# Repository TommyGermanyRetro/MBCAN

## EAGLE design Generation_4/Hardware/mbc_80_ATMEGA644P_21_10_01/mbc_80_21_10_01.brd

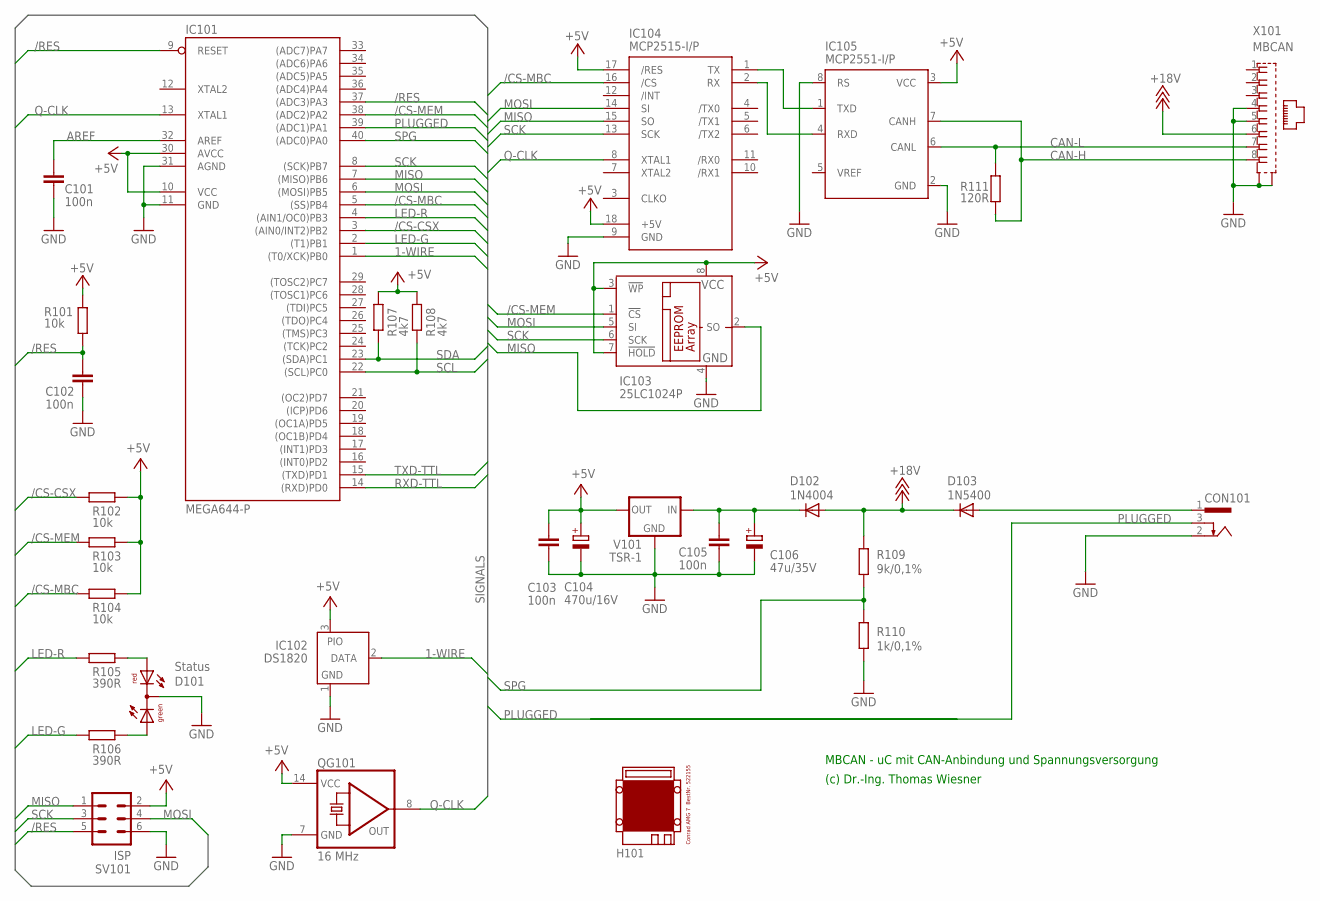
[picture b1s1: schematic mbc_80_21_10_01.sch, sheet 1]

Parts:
C101, C102, C103, C105: 100n; C025-025X050
C104: 470u/16V; E3,5-8
C106: 47u/35V; E2,5-7
CON101: POWER-JACK
D101: Status; DUOLED5MM
D102: 1N4004; DO41-10
D103: 1N5400; DO201-15
H101: MODULGEHÄUSE-AMG-7
IC101: MEGA644-P; DIL40
IC102: DS1820; TO92-
IC103: 25LC1024P; DIL8
IC104: MCP2515-I/P; DIL18
IC105: MCP2551-I/P; DIL08
QG101: 16 MHz; DIL14S
R101, R102, R103, R104: 10k; 0207/10
R105, R106: 390R; 0207/10
R107, R108: 4k7; 0207/10
R109: 9k/0,1%; 0207/10
R110: 1k/0,1%; 0207/10
R111: 120R; 0207/10
SV101: ISP; ML6
V101: TSR-1; TRACO-TSR-1
X101: MBCAN; 0446200002

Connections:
1-WIRE: IC101.1 ((T0/XCK)PB0), IC102.2 (DATA)
+5V: C103.1, C104.+, IC101.10 (VCC), IC101.30 (AVCC), IC102.3 (PIO), IC103.3 (!WP), IC103.7 (!HOLD), IC103.8 (VCC), IC104.17 (/RES), IC104.18 (+5V), IC105.3 (VCC), QG101.14 (VCC), R101.2, R102.2, R103.2, R104.2, R107.2, R108.2, SV101.2, V101.OUT; also elsewhere on the board
+18V: D102.A, D103.C, R109.1, X101.6
/CS-CSX: IC101.3 ((AIN0/INT2)PB2), R102.1; also elsewhere on the board
/CS-MBC: IC101.5 ((SS)PB4), IC104.16 (/CS), R104.1
/CS-MEM: IC101.38 ((ADC2)PA2), IC103.1 (!CS), R103.1
/RES: C102.1, IC101.9 (RESET), IC101.37 ((ADC3)PA3), R101.1, SV101.5
AREF: C101.1, IC101.32 (AREF)
CAN-H: IC105.7 (CANH), R111.1, X101.8
CAN-L: IC105.6 (CANL), R111.2, X101.7
GND: C101.2, C102.2, C103.2, C104.-, C105.2, C106.-, CON101.2, D101.K (C), IC101.11 (GND), IC101.31 (AGND), IC102.1 (GND), IC103.4 (GND), IC104.9 (GND), IC105.2 (GND), IC105.8 (RS), QG101.7 (GND), R110.2, SV101.6, V101.GND, X101.4, X101.5, X101.S@1 (S1), X101.S@2 (S2); also elsewhere on the board
LED-G: IC101.2 ((T1)PB1), R106.1
LED-R: IC101.4 ((AIN1/OC0)PB3), R105.1
MISO: IC101.7 ((MISO)PB6), IC103.2 (SO), IC104.15 (SO), SV101.1; also elsewhere on the board
MOSI: IC101.6 ((MOSI)PB5), IC103.5 (SI), IC104.14 (SI), SV101.4; also elsewhere on the board
unnamed: IC104.1 (TX), IC105.1 (TXD)
unnamed: IC104.2 (RX), IC105.4 (RXD)
unnamed: C105.1, C106.+, D102.C, V101.IN
unnamed: D101.AR, R105.2
unnamed: D101.AG, R106.2
PLUGGED: CON101.3, IC101.39 ((ADC1)PA1)
Q-CLK: IC101.13 (XTAL1), IC104.8 (XTAL1), QG101.8 (OUT); also elsewhere on the board
RXD-TTL: IC101.14 ((RXD)PD0); also elsewhere on the board
SCK: IC101.8 ((SCK)PB7), IC103.6 (SCK), IC104.13 (SCK), SV101.3; also elsewhere on the board
SCL: IC101.22 ((SCL)PC0), R108.1; also elsewhere on the board
SDA: IC101.23 ((SDA)PC1), R107.1; also elsewhere on the board
SPG: IC101.40 ((ADC0)PA0), R109.2, R110.1
TXD-TTL: IC101.15 ((TXD)PD1); also elsewhere on the board
V-NETZTEIL: CON101.1, D103.A

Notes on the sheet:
MBCAN - uC mit CAN-Anbindung und Spannungsversorgung
(c) Dr.-Ing. Thomas Wiesner

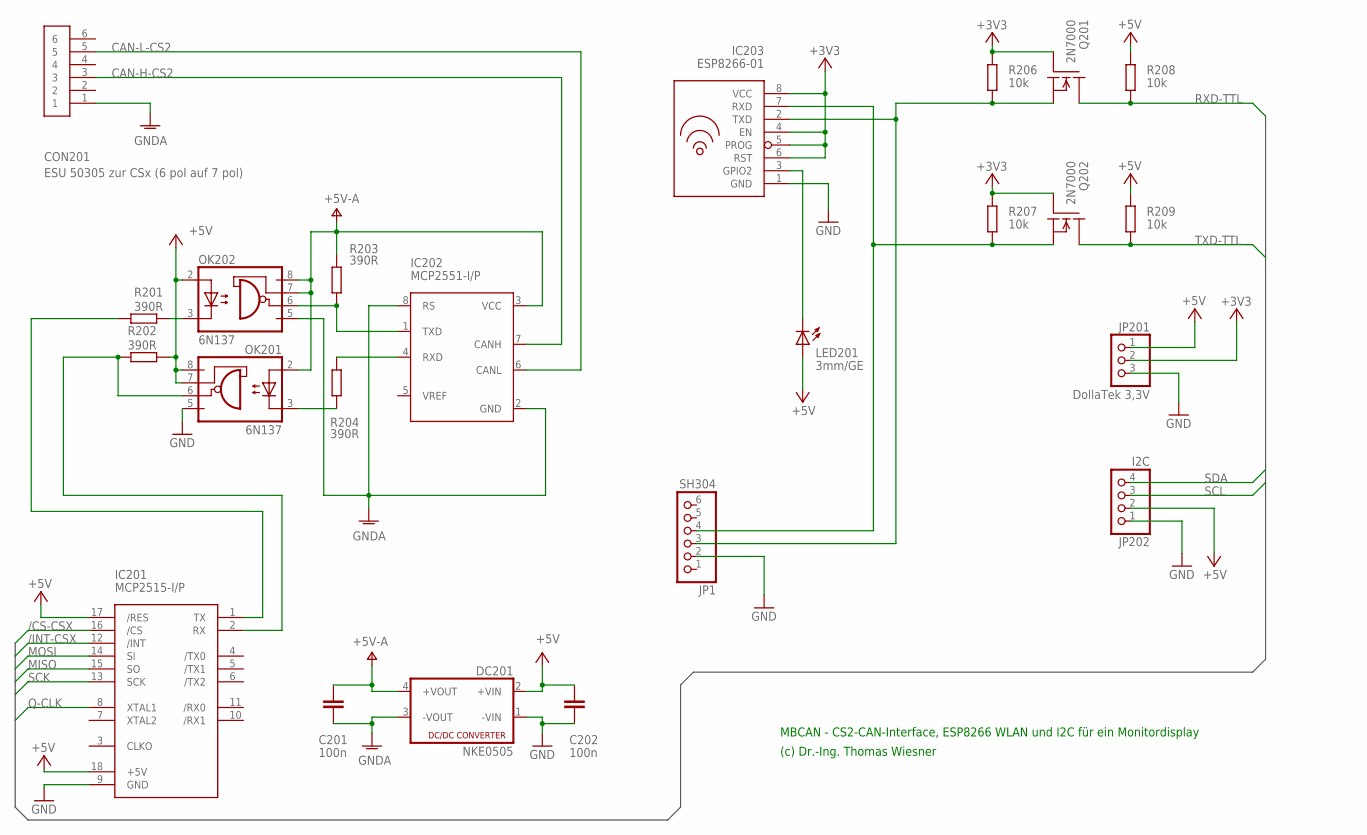
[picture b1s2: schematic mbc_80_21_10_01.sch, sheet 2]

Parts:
C201, C202: 100n; C025-025X050
CON201: ESU 50305 zur CSx (6 pol auf 7 pol); MINI-DIN-6-POL
DC201: NKE0505; NME
IC201: MCP2515-I/P; DIL18
IC202: MCP2551-I/P; DIL08
IC203: ESP8266-01
JP1: SH304; 1X06
JP201: DollaTek 3,3V; 1X03
JP202: I2C; 1X04
LED201: 3mm/GE; LED3MM
OK201, OK202: 6N137; DIL08
Q201, Q202: 2N7000; TO-92
R201, R202, R203, R204: 390R; 0207/10
R206, R207, R208, R209: 10k; 0207/10

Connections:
+3V3: IC203.4 (EN), IC203.5 (PROG), IC203.6 (RST), IC203.8 (VCC), JP201.2, Q201.2 (G), Q202.2 (G), R206.2, R207.2
+5V: C202.1, DC201.2 (+VIN), IC201.17 (/RES), IC201.18 (+5V), JP201.1, JP202.2, LED201.A, OK201.7 (VE), OK201.8 (VCC), OK202.2 (A), R202.2, R208.2, R209.2; also elsewhere on the board
+5V-A: C201.1, DC201.4 (+VOUT), IC202.3 (VCC), OK201.2 (A), OK202.7 (VE), OK202.8 (VCC), R203.2
/CS-CSX: IC201.16 (/CS); also elsewhere on the board
/INT-CSX: IC201.12 (/INT)
CAN-H-CS2: CON201.3, IC202.7 (CANH)
CAN-L-CS2: CON201.5, IC202.6 (CANL)
GND: C202.2, DC201.1 (-VIN), IC201.9 (GND), IC203.1 (GND), JP1.2, JP201.3, JP202.1, OK201.5 (GND); also elsewhere on the board
GNDA: C201.2, CON201.1, DC201.3 (-VOUT), IC202.2 (GND), IC202.8 (RS), OK202.5 (GND)
MISO: IC201.15 (SO); also elsewhere on the board
MOSI: IC201.14 (SI); also elsewhere on the board
unnamed: IC203.3 (GPIO2), LED201.K (C)
unnamed: IC203.2 (TXD), JP1.3, Q201.1 (S), R206.1
unnamed: IC203.7 (RXD), JP1.4, Q202.1 (S), R207.1
unnamed: IC201.1 (TX), R201.2
unnamed: IC202.1 (TXD), OK202.6 (VO), R203.1
unnamed: OK201.3 (C), R204.1
unnamed: IC202.4 (RXD), R204.2
unnamed: OK202.3 (C), R201.1
unnamed: IC201.2 (RX), OK201.6 (VO), R202.1
Q-CLK: IC201.8 (XTAL1); also elsewhere on the board
RXD-TTL: Q201.3 (D), R208.1; also elsewhere on the board
SCK: IC201.13 (SCK); also elsewhere on the board
SCL: JP202.3; also elsewhere on the board
SDA: JP202.4; also elsewhere on the board
TXD-TTL: Q202.3 (D), R209.1; also elsewhere on the board

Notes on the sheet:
(c) Dr.-Ing. Thomas Wiesner
MBCAN - CS2-CAN-Interface, ESP8266 WLAN und I2C für ein Monitordisplay

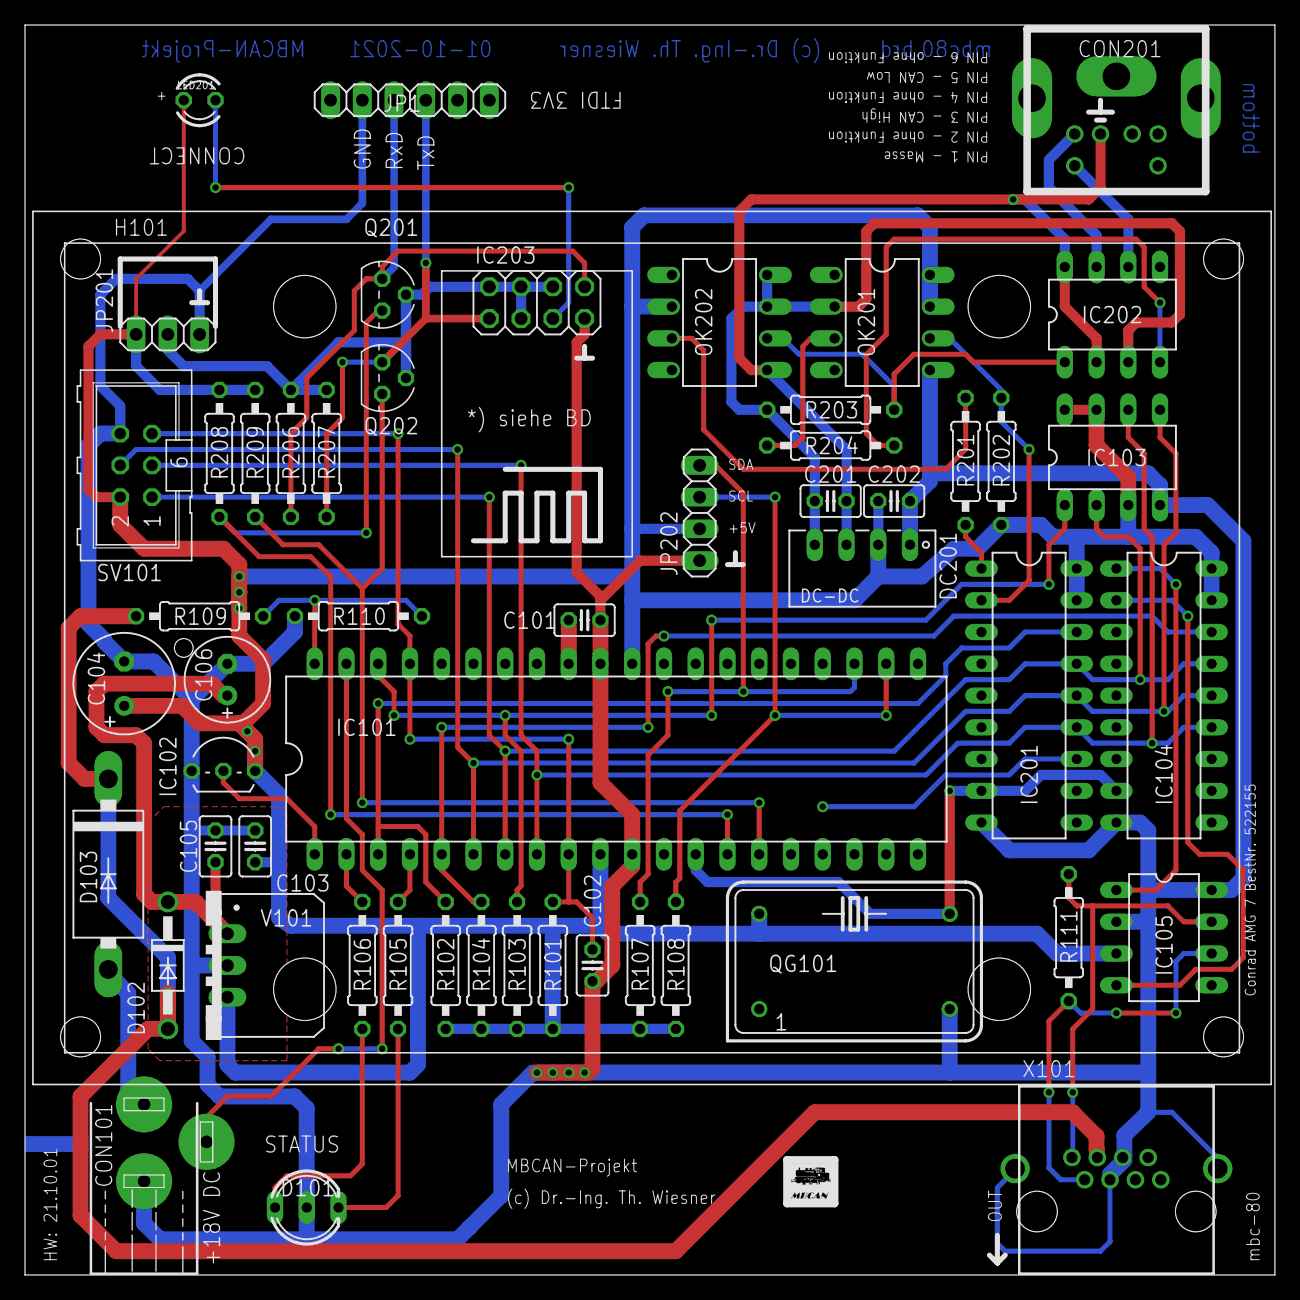
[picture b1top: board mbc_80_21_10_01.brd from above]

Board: 2 copper layers, 100.0 x 100.0 mm, 54 parts (0 on the bottom side), 43 nets.

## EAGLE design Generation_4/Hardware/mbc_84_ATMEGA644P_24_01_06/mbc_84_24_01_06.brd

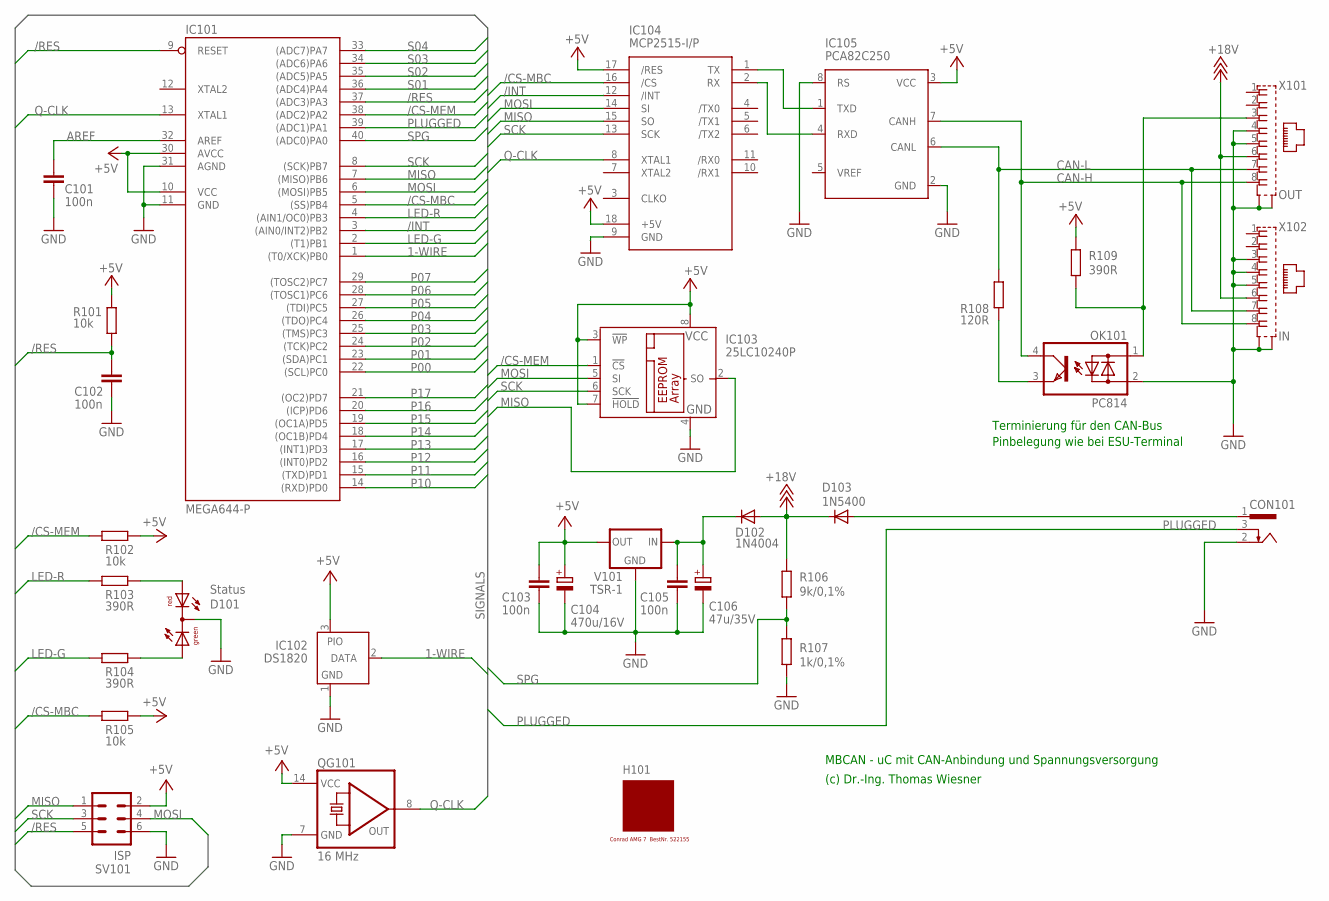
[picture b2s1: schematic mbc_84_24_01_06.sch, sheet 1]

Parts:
C101, C102, C103, C105: 100n; C025-025X050
C104: 470u/16V; E3,5-8
C106: 47u/35V; E2,5-7
CON101: POWER-JACK
D101: Status; DUOLED5MM
D102: 1N4004; DO41-10
D103: 1N5400; DO201-15
H101: MODULGEHÄUSE-AMG-7; MODULGEHÄUSE-1
IC101: MEGA644-P; DIL40
IC102: DS1820; TO92-
IC103: 25LC10240P; DIL8
IC104: MCP2515-I/P; DIL18
IC105: PCA82C250; DIL08
OK101: PC814; DIL04
QG101: 16 MHz; DIL14S
R101, R102, R105: 10k; 0207/10
R103, R104, R109: 390R; 0207/10
R106: 9k/0,1%; 0207/10
R107: 1k/0,1%; 0207/10
R108: 120R; 0207/10
SV101: ISP; ML6
V101: TSR-1; TRACO-TSR-1
X101: OUT; 0446200002
X102: IN; 0446200002

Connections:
1-WIRE: IC101.1 ((T0/XCK)PB0), IC102.2 (DATA)
+5V: C103.1, C104.+, IC101.10 (VCC), IC101.30 (AVCC), IC102.3 (PIO), IC103.3 (!WP), IC103.7 (!HOLD), IC103.8 (VCC), IC104.17 (/RES), IC104.18 (+5V), IC105.3 (VCC), QG101.14 (VCC), R101.2, R102.2, R105.2, R109.1, SV101.2, V101.OUT; also elsewhere on the board
+18V: D102.A, D103.C, R106.1, X101.6, X102.6; also elsewhere on the board
/CS-MBC: IC101.5 ((SS)PB4), IC104.16 (/CS), R105.1
/CS-MEM: IC101.38 ((ADC2)PA2), IC103.1 (!CS), R102.1
/INT: IC101.3 ((AIN0/INT2)PB2), IC104.12 (/INT)
/RES: C102.1, IC101.9 (RESET), IC101.37 ((ADC3)PA3), R101.1, SV101.5
AREF: C101.1, IC101.32 (AREF)
CAN-H: IC105.7 (CANH), OK101.4 (C), X101.8, X102.8
CAN-L: IC105.6 (CANL), R108.2, X101.7, X102.7
GND: C101.2, C102.2, C103.2, C104.-, C105.2, C106.-, CON101.2, D101.K (C), IC101.11 (GND), IC101.31 (AGND), IC102.1 (GND), IC103.4 (GND), IC104.9 (GND), IC105.2 (GND), IC105.8 (RS), OK101.2 (AC2), QG101.7 (GND), R107.2, SV101.6, V101.GND, X101.4, X101.5, X101.S@1 (S1), X101.S@2 (S2), X102.3, X102.4, X102.5, X102.S@1 (S1), X102.S@2 (S2); also elsewhere on the board
LED-G: IC101.2 ((T1)PB1), R104.1
LED-R: IC101.4 ((AIN1/OC0)PB3), R103.1
MISO: IC101.7 ((MISO)PB6), IC103.2 (SO), IC104.15 (SO), SV101.1
MOSI: IC101.6 ((MOSI)PB5), IC103.5 (SI), IC104.14 (SI), SV101.4
unnamed: IC104.1 (TX), IC105.1 (TXD)
unnamed: IC104.2 (RX), IC105.4 (RXD)
unnamed: OK101.3 (E), R108.1
unnamed: OK101.1 (AC1), R109.2, X101.3
unnamed: C105.1, C106.+, D102.C, V101.IN
unnamed: D101.AR, R103.2
unnamed: D101.AG, R104.2
P00: IC101.22 ((SCL)PC0); also elsewhere on the board
P01: IC101.23 ((SDA)PC1); also elsewhere on the board
P02: IC101.24 ((TCK)PC2); also elsewhere on the board
P03: IC101.25 ((TMS)PC3); also elsewhere on the board
P04: IC101.26 ((TDO)PC4); also elsewhere on the board
P05: IC101.27 ((TDI)PC5); also elsewhere on the board
P06: IC101.28 ((TOSC1)PC6); also elsewhere on the board
P07: IC101.29 ((TOSC2)PC7); also elsewhere on the board
P10: IC101.14 ((RXD)PD0); also elsewhere on the board
P11: IC101.15 ((TXD)PD1); also elsewhere on the board
P12: IC101.16 ((INT0)PD2); also elsewhere on the board
P13: IC101.17 ((INT1)PD3); also elsewhere on the board
P14: IC101.18 ((OC1B)PD4); also elsewhere on the board
P15: IC101.19 ((OC1A)PD5); also elsewhere on the board
P16: IC101.20 ((ICP)PD6); also elsewhere on the board
P17: IC101.21 ((OC2)PD7); also elsewhere on the board
PLUGGED: CON101.3, IC101.39 ((ADC1)PA1)
Q-CLK: IC101.13 (XTAL1), IC104.8 (XTAL1), QG101.8 (OUT)
S01: IC101.36 ((ADC4)PA4); also elsewhere on the board
S02: IC101.35 ((ADC5)PA5); also elsewhere on the board
S03: IC101.34 ((ADC6)PA6); also elsewhere on the board
S04: IC101.33 ((ADC7)PA7); also elsewhere on the board
SCK: IC101.8 ((SCK)PB7), IC103.6 (SCK), IC104.13 (SCK), SV101.3
SPG: IC101.40 ((ADC0)PA0), R106.2, R107.1
V-NETZTEIL1: CON101.1, D103.A

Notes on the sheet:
MBCAN - uC mit CAN-Anbindung und Spannungsversorgung
(c) Dr.-Ing. Thomas Wiesner
Terminierung für den CAN-Bus
Pinbelegung wie bei ESU-Terminal

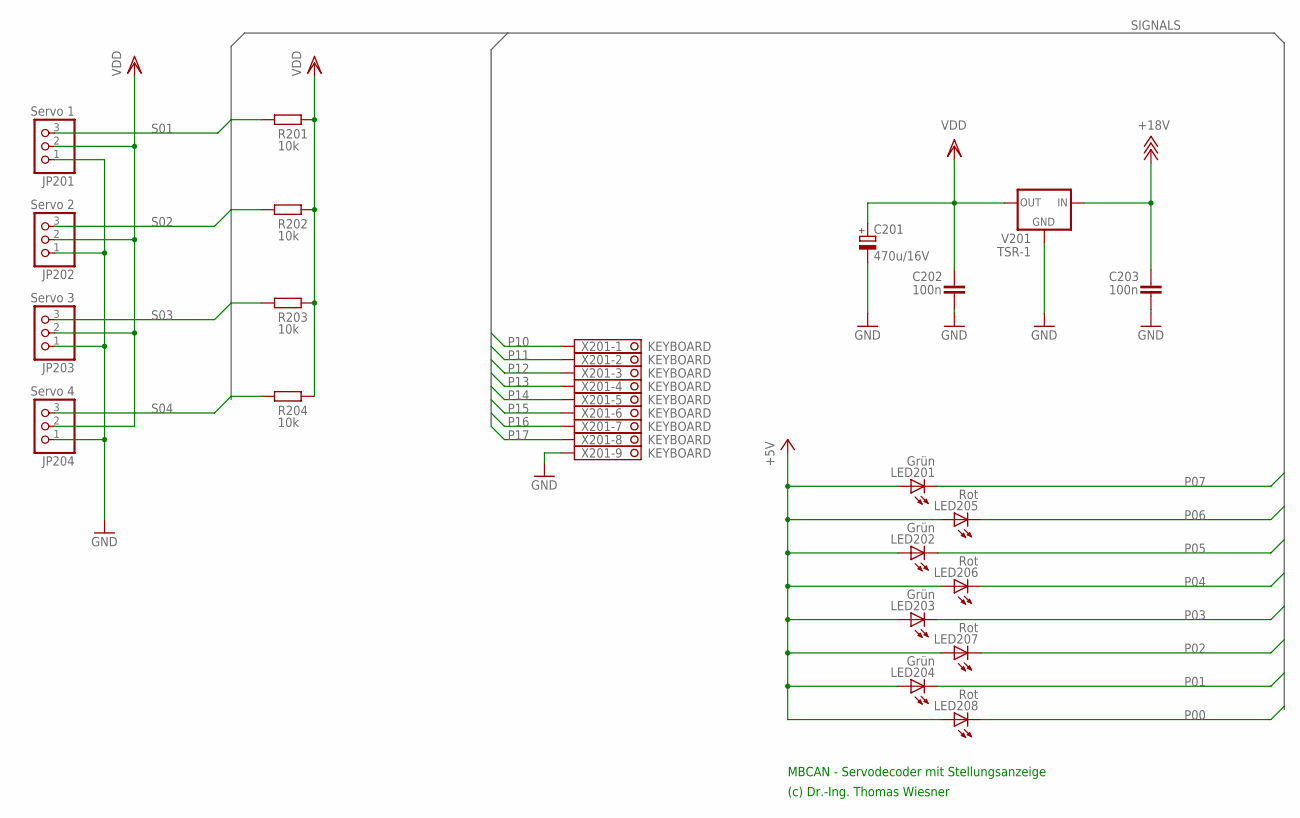
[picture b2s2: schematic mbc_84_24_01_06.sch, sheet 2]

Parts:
C201: 470u/16V; E3,5-8
C202, C203: 100n; C025-025X050
JP201: Servo 1; 1X03
JP202: Servo 2; 1X03
JP203: Servo 3; 1X03
JP204: Servo 4; 1X03
LED201, LED202, LED203, LED204: Grün; LED3MM
LED205, LED206, LED207, LED208: Rot; LED3MM
R201, R202, R203, R204: 10k; 0207/10
V201: TSR-1; TRACO-TSR-1
X201: KEYBOARD; 1751316

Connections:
+5V: LED201.A, LED202.A, LED203.A, LED204.A, LED205.A, LED206.A, LED207.A, LED208.A; also elsewhere on the board
+18V: C203.1, V201.IN; also elsewhere on the board
GND: C201.-, C202.2, C203.2, JP201.1, JP202.1, JP203.1, JP204.1, V201.GND, X201.9; also elsewhere on the board
P00: LED208.K (C); also elsewhere on the board
P01: LED204.K (C); also elsewhere on the board
P02: LED207.K (C); also elsewhere on the board
P03: LED203.K (C); also elsewhere on the board
P04: LED206.K (C); also elsewhere on the board
P05: LED202.K (C); also elsewhere on the board
P06: LED205.K (C); also elsewhere on the board
P07: LED201.K (C); also elsewhere on the board
P10: X201.1; also elsewhere on the board
P11: X201.2; also elsewhere on the board
P12: X201.3; also elsewhere on the board
P13: X201.4; also elsewhere on the board
P14: X201.5; also elsewhere on the board
P15: X201.6; also elsewhere on the board
P16: X201.7; also elsewhere on the board
P17: X201.8; also elsewhere on the board
S01: JP201.3, R201.1; also elsewhere on the board
S02: JP202.3, R202.1; also elsewhere on the board
S03: JP203.3, R203.1; also elsewhere on the board
S04: JP204.3, R204.1; also elsewhere on the board
VDD: C201.+, C202.1, JP201.2, JP202.2, JP203.2, JP204.2, R201.2, R202.2, R203.2, R204.2, V201.OUT

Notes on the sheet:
MBCAN - Servodecoder mit Stellungsanzeige
(c) Dr.-Ing. Thomas Wiesner

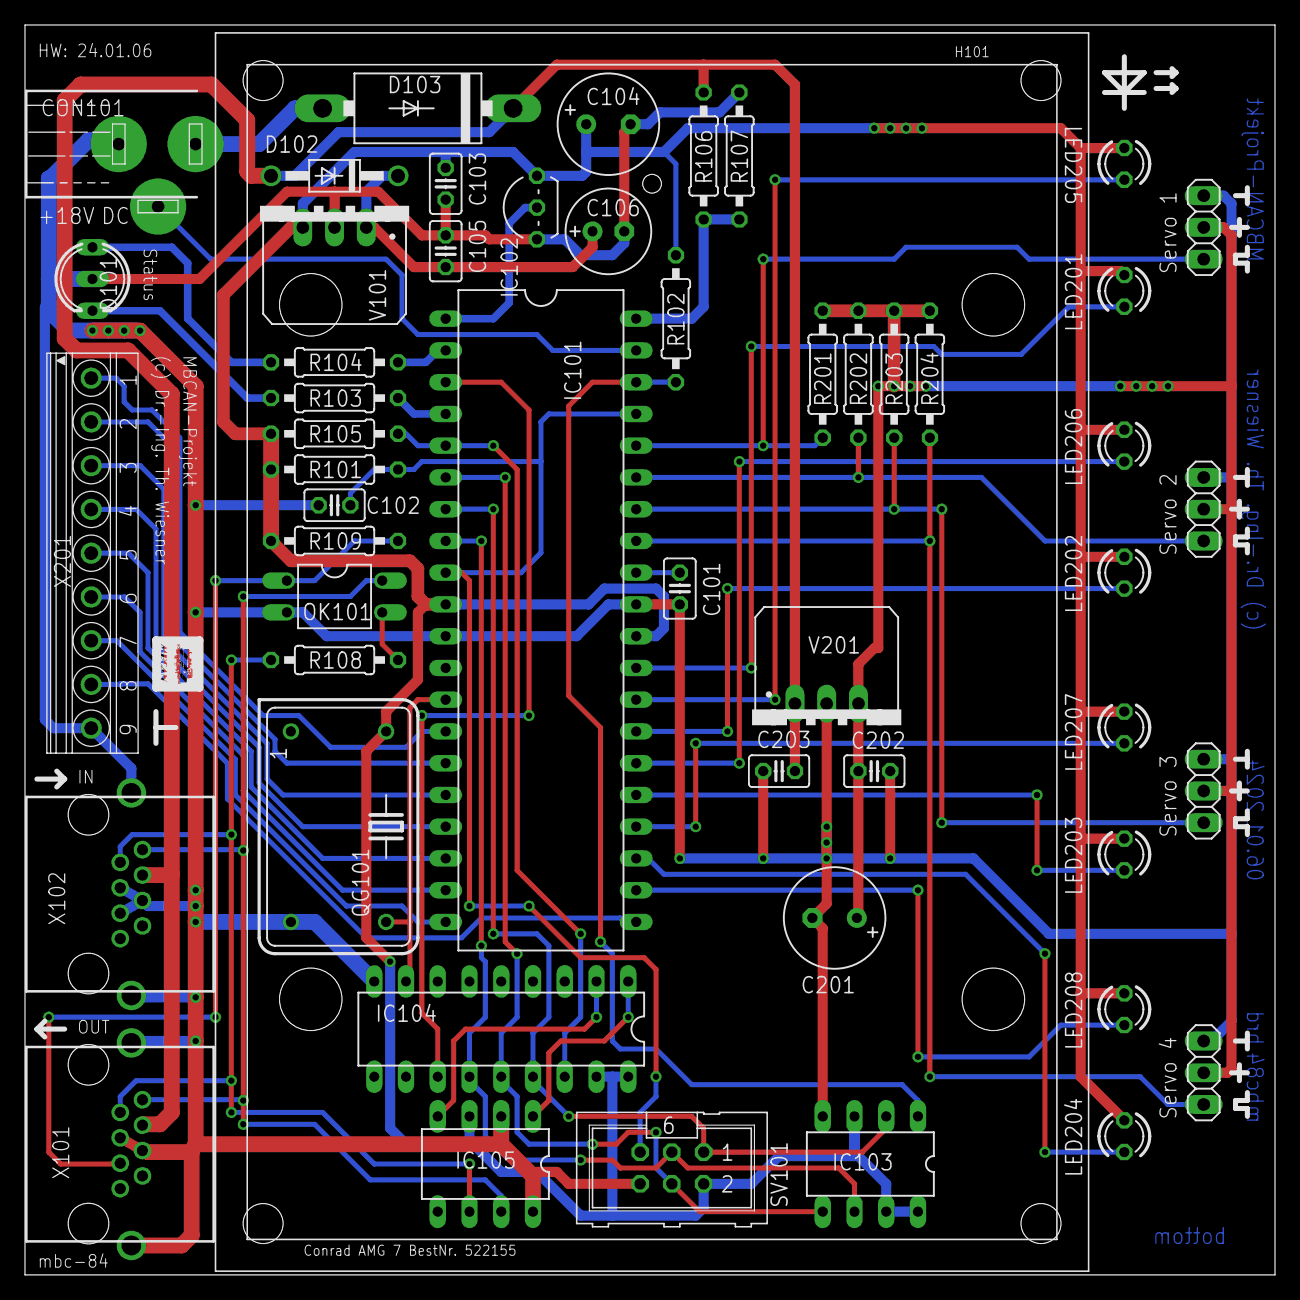
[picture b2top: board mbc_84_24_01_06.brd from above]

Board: 2 copper layers, 100.0 x 100.0 mm, 52 parts (0 on the bottom side), 48 nets.

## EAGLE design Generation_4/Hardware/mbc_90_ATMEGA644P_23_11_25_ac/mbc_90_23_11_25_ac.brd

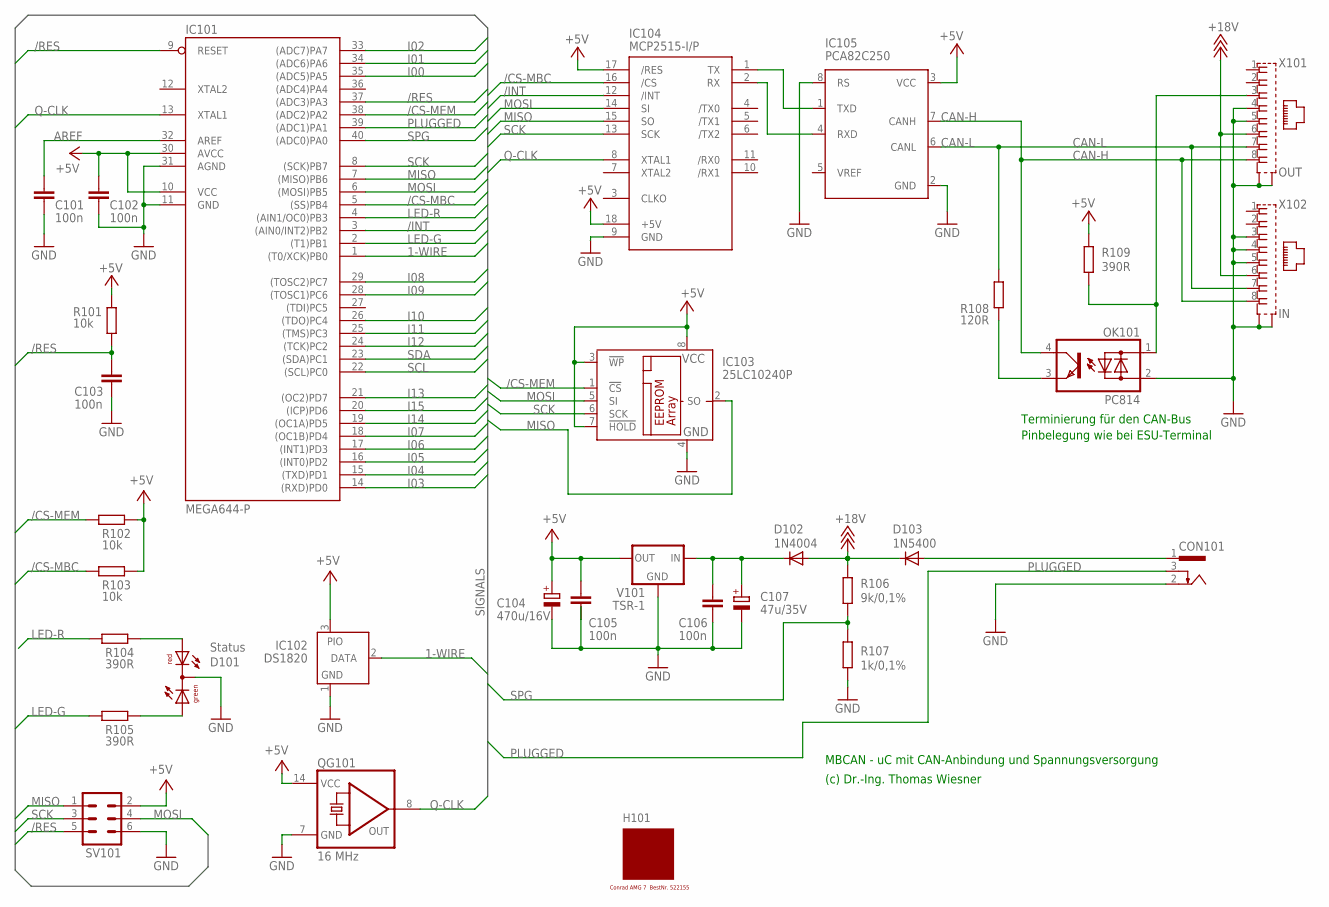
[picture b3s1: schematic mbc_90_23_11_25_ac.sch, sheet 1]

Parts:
C101, C102, C103, C105, C106: 100n; C025-025X050
C104: 470u/16V; E3,5-8
C107: 47u/35V; E2,5-7
CON101: POWER-JACK
D101: Status; DUOLED5MM
D102: 1N4004; DO41-10
D103: 1N5400; DO201-15
H101: MODULGEHÄUSE-AMG-7; MODULGEHÄUSE-1
IC101: MEGA644-P; DIL40
IC102: DS1820; TO92-
IC103: 25LC10240P; DIL8
IC104: MCP2515-I/P; DIL18
IC105: PCA82C250; DIL08
OK101: PC814; DIL04
QG101: 16 MHz; DIL14S
R101, R102, R103: 10k; 0207/10
R104, R105, R109: 390R; 0207/10
R106: 9k/0,1%; 0207/10
R107: 1k/0,1%; 0207/10
R108: 120R; 0207/10
SV101: ML6
V101: TSR-1; TRACO-TSR-1
X101: OUT; 0446200002
X102: IN; 0446200002

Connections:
1-WIRE: IC101.1 ((T0/XCK)PB0), IC102.2 (DATA)
+5V: C102.1, C104.+, C105.1, IC101.10 (VCC), IC101.30 (AVCC), IC102.3 (PIO), IC103.3 (!WP), IC103.7 (!HOLD), IC103.8 (VCC), IC104.17 (/RES), IC104.18 (+5V), IC105.3 (VCC), QG101.14 (VCC), R101.2, R102.2, R103.2, R109.1, SV101.2, V101.OUT; also elsewhere on the board
+18V: D102.A, D103.C, R106.1, X101.6, X102.6
/CS-MBC: IC101.5 ((SS)PB4), IC104.16 (/CS), R103.1
/CS-MEM: IC101.38 ((ADC2)PA2), IC103.1 (!CS), R102.1
/INT: IC101.3 ((AIN0/INT2)PB2), IC104.12 (/INT)
/RES: C103.1, IC101.9 (RESET), IC101.37 ((ADC3)PA3), R101.1, SV101.5
AREF: C101.1, IC101.32 (AREF)
CAN-H: IC105.7 (CANH), OK101.4 (C), X101.8, X102.8
CAN-L: IC105.6 (CANL), R108.2, X101.7, X102.7
GND: C101.2, C102.2, C103.2, C104.-, C105.2, C106.2, C107.-, CON101.2, D101.K (C), IC101.11 (GND), IC101.31 (AGND), IC102.1 (GND), IC103.4 (GND), IC104.9 (GND), IC105.2 (GND), IC105.8 (RS), QG101.7 (GND), R107.2, SV101.6, V101.GND, X101.4, X101.5, X101.S@1 (S1), X101.S@2 (S2), X102.3, X102.4, X102.5, X102.S@1 (S1), X102.S@2 (S2); also elsewhere on the board
I00: IC101.35 ((ADC5)PA5); also elsewhere on the board
I01: IC101.34 ((ADC6)PA6); also elsewhere on the board
I02: IC101.33 ((ADC7)PA7); also elsewhere on the board
I03: IC101.14 ((RXD)PD0); also elsewhere on the board
I04: IC101.15 ((TXD)PD1); also elsewhere on the board
I05: IC101.16 ((INT0)PD2); also elsewhere on the board
I06: IC101.17 ((INT1)PD3); also elsewhere on the board
I07: IC101.18 ((OC1B)PD4); also elsewhere on the board
I08: IC101.29 ((TOSC2)PC7); also elsewhere on the board
I09: IC101.28 ((TOSC1)PC6); also elsewhere on the board
I10: IC101.26 ((TDO)PC4); also elsewhere on the board
I11: IC101.25 ((TMS)PC3); also elsewhere on the board
I12: IC101.24 ((TCK)PC2); also elsewhere on the board
I13: IC101.21 ((OC2)PD7); also elsewhere on the board
I14: IC101.19 ((OC1A)PD5); also elsewhere on the board
I15: IC101.20 ((ICP)PD6); also elsewhere on the board
LED-G: IC101.2 ((T1)PB1), R105.1
LED-R: IC101.4 ((AIN1/OC0)PB3), R104.1
MISO: IC101.7 ((MISO)PB6), IC103.2 (SO), IC104.15 (SO), SV101.1
MOSI: IC101.6 ((MOSI)PB5), IC103.5 (SI), IC104.14 (SI), SV101.4
unnamed: IC104.1 (TX), IC105.1 (TXD)
unnamed: IC104.2 (RX), IC105.4 (RXD)
unnamed: OK101.3 (E), R108.1
unnamed: C106.1, C107.+, D102.C, V101.IN
unnamed: OK101.1 (AC1), R109.2, X101.3
unnamed: D101.AR, R104.2
unnamed: D101.AG, R105.2
PLUGGED: CON101.3, IC101.39 ((ADC1)PA1)
Q-CLK: IC101.13 (XTAL1), IC104.8 (XTAL1), QG101.8 (OUT)
SCK: IC101.8 ((SCK)PB7), IC103.6 (SCK), IC104.13 (SCK), SV101.3
SCL: IC101.22 ((SCL)PC0); also elsewhere on the board
SDA: IC101.23 ((SDA)PC1); also elsewhere on the board
SPG: IC101.40 ((ADC0)PA0), R106.2, R107.1
V-NETZTEIL1: CON101.1, D103.A

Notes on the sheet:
MBCAN - uC mit CAN-Anbindung und Spannungsversorgung
(c) Dr.-Ing. Thomas Wiesner
Terminierung für den CAN-Bus
Pinbelegung wie bei ESU-Terminal

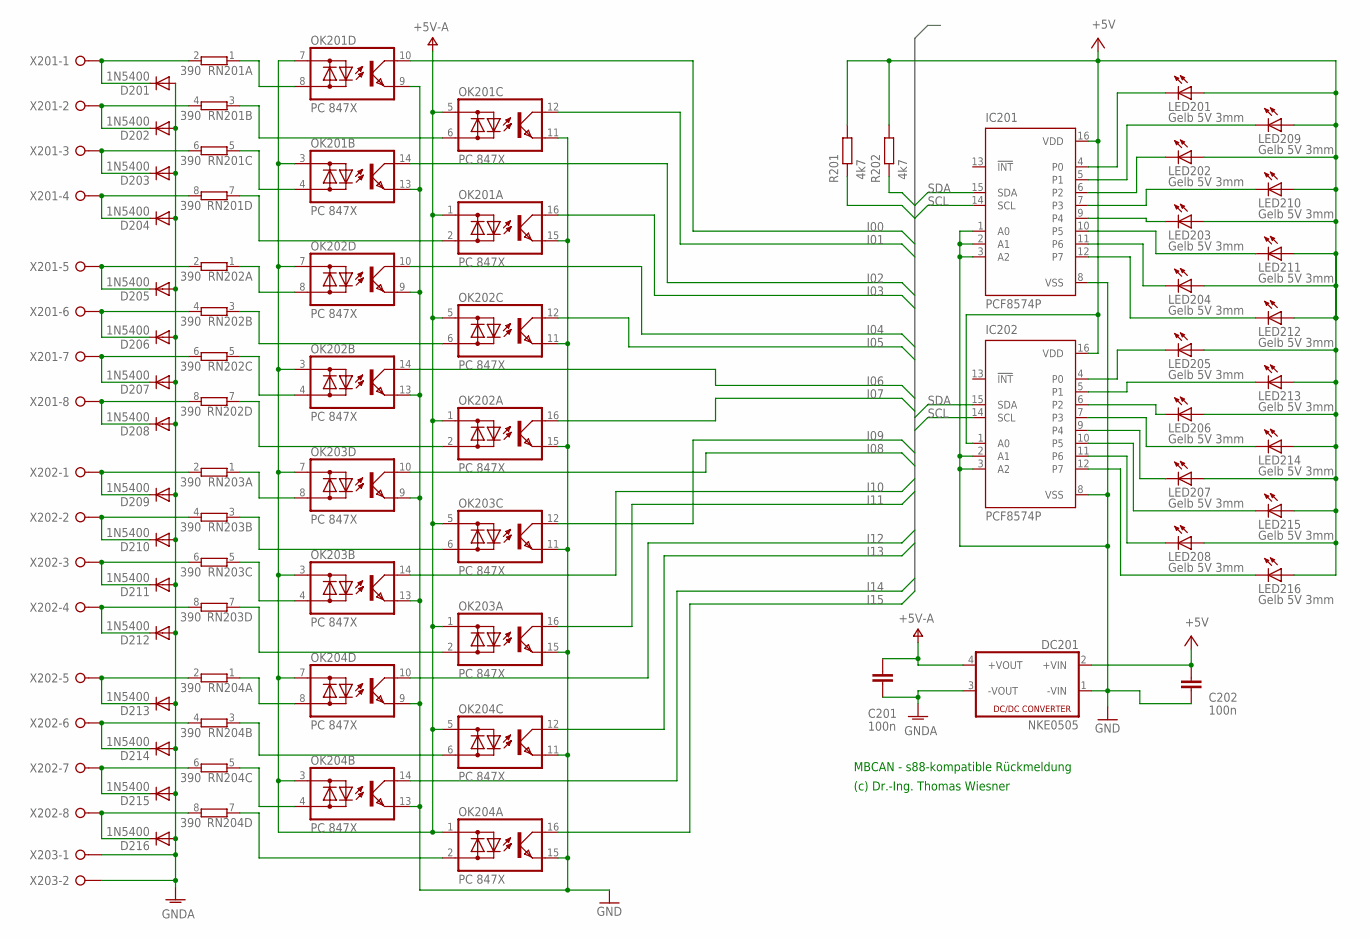
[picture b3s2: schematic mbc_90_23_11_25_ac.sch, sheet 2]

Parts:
C201, C202: 100n; C025-025X050
D201, D202, D203, D204, D205, D206, D207, D208, D209, D210, D211, D212, D213, D214, D215, D216: 1N5400; DO201-15
DC201: NKE0505; NME
IC201, IC202: PCF8574P; DIL16
LED201, LED202, LED203, LED204, LED205, LED206, LED207, LED208, LED209, LED210, LED211, LED212, LED213, LED214, LED215, LED216: Gelb 5V 3mm; LED3MM
OK201, OK202, OK203, OK204: PC 847X; DIL16
R201, R202: 4k7; 0207/10
RN201, RN202, RN203, RN204: 390; SIL8
X201, X202: W237-08P; W237-8P
X203: W237-02P; W237-132

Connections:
+5V: C202.1, DC201.2 (+VIN), IC201.16 (VDD), IC202.1 (A0), IC202.16 (VDD), LED201.A, LED202.A, LED203.A, LED204.A, LED205.A, LED206.A, LED207.A, LED208.A, LED209.A, LED210.A, LED211.A, LED212.A, LED213.A, LED214.A, LED215.A, LED216.A, R201.2, R202.2; also elsewhere on the board
GND: C202.2, DC201.1 (-VIN), IC201.1 (A0), IC201.2 (A1), IC201.3 (A2), IC201.8 (VSS), IC202.2 (A1), IC202.3 (A2), IC202.8 (VSS), OK201.9 (E), OK201.11 (E), OK201.13 (E), OK201.15 (E), OK202.9 (E), OK202.11 (E), OK202.13 (E), OK202.15 (E), OK203.9 (E), OK203.11 (E), OK203.13 (E), OK203.15 (E), OK204.9 (E), OK204.11 (E), OK204.13 (E), OK204.15 (E); also elsewhere on the board
GNDA: C201.2, D201.A, D202.A, D203.A, D204.A, D205.A, D206.A, D207.A, D208.A, D209.A, D210.A, D211.A, D212.A, D213.A, D214.A, D215.A, D216.A, DC201.3 (-VOUT), X203.1, X203.2
I00: OK201.10 (C); also elsewhere on the board
I01: OK201.12 (C); also elsewhere on the board
I02: OK201.14 (C); also elsewhere on the board
I03: OK201.16 (C); also elsewhere on the board
I04: OK202.10 (C); also elsewhere on the board
I05: OK202.12 (C); also elsewhere on the board
I06: OK202.14 (C); also elsewhere on the board
I07: OK202.16 (C); also elsewhere on the board
I08: OK203.10 (C); also elsewhere on the board
I09: OK203.12 (C); also elsewhere on the board
I10: OK203.14 (C); also elsewhere on the board
I11: OK203.16 (C); also elsewhere on the board
I12: OK204.10 (C); also elsewhere on the board
I13: OK204.12 (C); also elsewhere on the board
I14: OK204.14 (C); also elsewhere on the board
I15: OK204.16 (C); also elsewhere on the board
unnamed: IC201.9 (P4), LED203.K (C)
unnamed: D215.C, RN204.6 (2), X202.7
unnamed: D216.C, RN204.8 (2), X202.8
unnamed: D213.C, RN204.2, X202.5
unnamed: D214.C, RN204.4 (2), X202.6
unnamed: D211.C, RN203.6 (2), X202.3
unnamed: D212.C, RN203.8 (2), X202.4
unnamed: D209.C, RN203.2, X202.1
unnamed: D210.C, RN203.4 (2), X202.2
unnamed: D207.C, RN202.6 (2), X201.7
unnamed: D208.C, RN202.8 (2), X201.8
unnamed: D205.C, RN202.2, X201.5
unnamed: D206.C, RN202.4 (2), X201.6
unnamed: D203.C, RN201.6 (2), X201.3
unnamed: D204.C, RN201.8 (2), X201.4
unnamed: D201.C, RN201.2, X201.1
unnamed: IC201.10 (P5), LED211.K (C)
unnamed: OK204.2 (AC2), RN204.7 (1)
unnamed: OK204.4 (AC2), RN204.5 (1)
unnamed: OK204.6 (AC2), RN204.3 (1)
unnamed: OK204.8 (AC2), RN204.1
unnamed: OK203.2 (AC2), RN203.7 (1)
unnamed: OK203.4 (AC2), RN203.5 (1)
unnamed: OK203.6 (AC2), RN203.3 (1)
unnamed: OK203.8 (AC2), RN203.1
unnamed: OK202.2 (AC2), RN202.7 (1)
unnamed: OK202.4 (AC2), RN202.5 (1)
unnamed: OK202.6 (AC2), RN202.3 (1)
unnamed: OK202.8 (AC2), RN202.1
unnamed: OK201.2 (AC2), RN201.7 (1)
unnamed: D202.C, RN201.4 (2), X201.2
unnamed: OK201.4 (AC2), RN201.5 (1)
unnamed: IC202.4 (P0), LED205.K (C)
unnamed: IC201.4 (P0), LED201.K (C)
unnamed: IC201.5 (P1), LED209.K (C)
unnamed: IC201.6 (P2), LED202.K (C)
unnamed: IC201.7 (P3), LED210.K (C)
unnamed: IC201.11 (P6), LED204.K (C)
unnamed: IC201.12 (P7), LED212.K (C)
unnamed: IC202.9 (P4), LED207.K (C)
unnamed: IC202.5 (P1), LED213.K (C)
unnamed: IC202.6 (P2), LED206.K (C)
unnamed: IC202.7 (P3), LED214.K (C)
unnamed: IC202.10 (P5), LED215.K (C)
unnamed: IC202.11 (P6), LED208.K (C)
unnamed: IC202.12 (P7), LED216.K (C)
unnamed: OK201.6 (AC2), RN201.3 (1)
unnamed: OK201.8 (AC2), RN201.1
SCL: IC201.14 (SCL), IC202.14 (SCL), R201.1; also elsewhere on the board
SDA: IC201.15 (SDA), IC202.15 (SDA), R202.1; also elsewhere on the board
V+: C201.1, DC201.4 (+VOUT), OK201.1 (AC1), OK201.3 (AC1), OK201.5 (AC1), OK201.7 (AC1), OK202.1 (AC1), OK202.3 (AC1), OK202.5 (AC1), OK202.7 (AC1), OK203.1 (AC1), OK203.3 (AC1), OK203.5 (AC1), OK203.7 (AC1), OK204.1 (AC1), OK204.3 (AC1), OK204.5 (AC1), OK204.7 (AC1)

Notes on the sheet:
MBCAN - s88-kompatible Rückmeldung
(c) Dr.-Ing. Thomas Wiesner

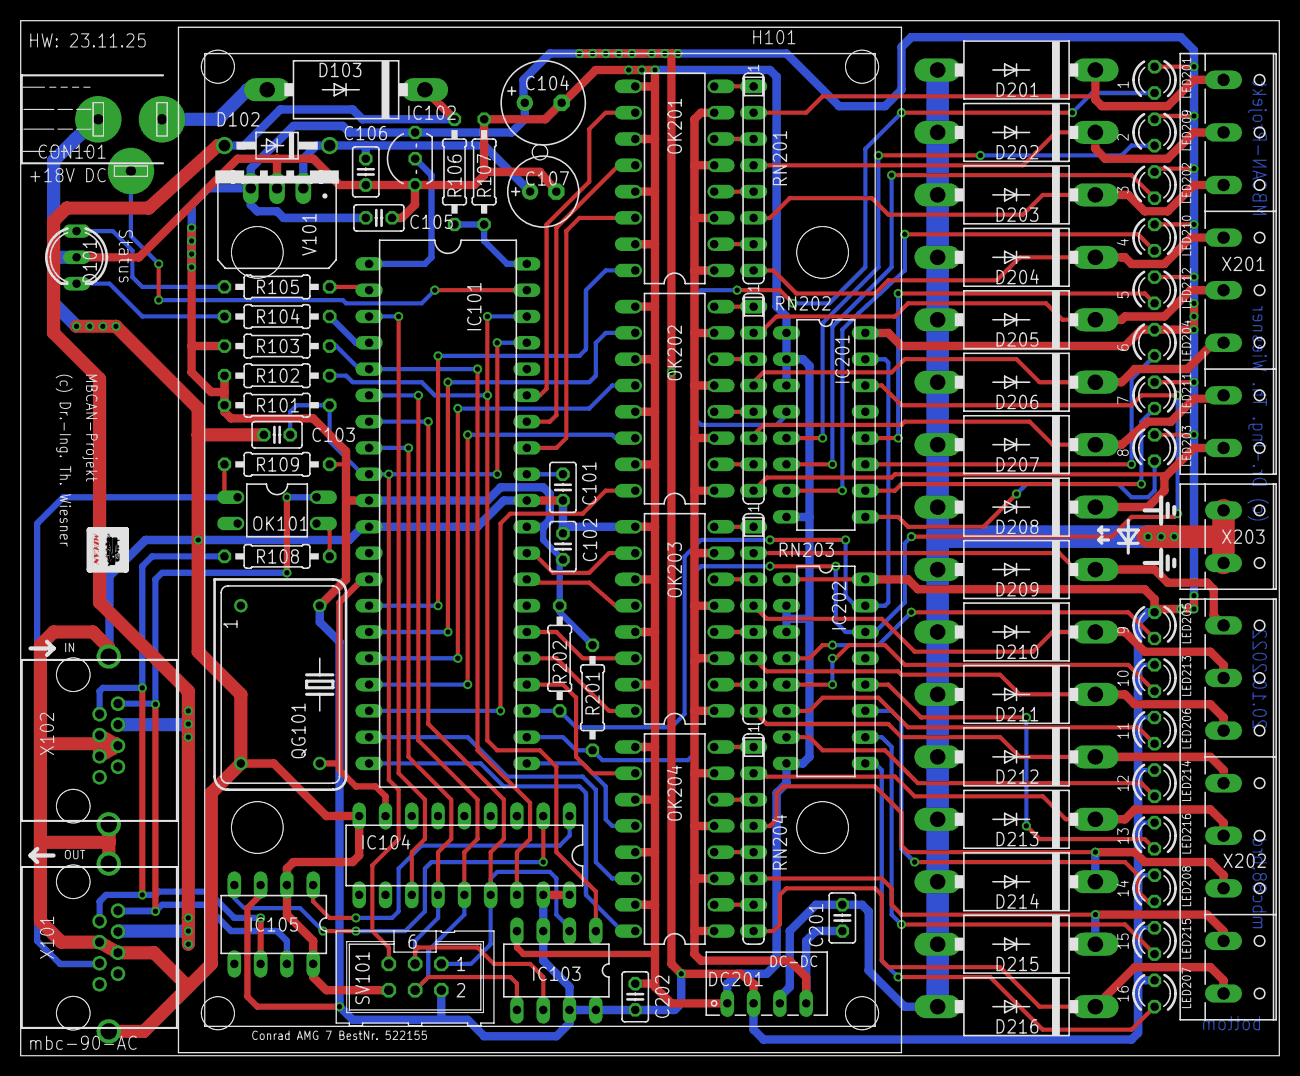
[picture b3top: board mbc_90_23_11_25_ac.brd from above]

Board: 2 copper layers, 121.6 x 100.0 mm, 82 parts (0 on the bottom side), 95 nets.
